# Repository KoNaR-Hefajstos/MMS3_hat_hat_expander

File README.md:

# Hat hat expander

## Sekcja 0: Jak szybko, dobrze i tanio zrobić hata z dokumentacją

Szybka lista punkcików to wyklepania zanim hat magicznie się zrobi

1. **Sprawdź istniejące projekty:** Zobacz czy nie ma już jakiegoś hata który robi co potrzebujesz. Zobacz w forkach i poszukaj na githubie po hashtag'ach, jeśli nie to
2. **Utwórz Fork:** Kliknij przycisk **Fork** w prawym górnym rogu tego repozytorium.

1. **Konfiguracja repozytorium:** Daj mu adekwatną nazwe, i z'clone'uj forka do siebie na pc
2. **Zasady projektowania:**
   * Dokładniejsza dokumentacja znajduje się w Sekcji 2.
   * Do komunikacji możesz używać **wyłącznie** interfejsów: **I2C, SPI oraz UART**.
   * Modyfikuj połączeń złącza chainbus, bus switch'a i EEPROM'a
   * Nie modyfikuj zarysu płytki, otworów montażowych ani pozycji złączy ChainBus.
   * Możesz usunąć złącze XT60, jeśli Twój projekt go nie wymaga.

### Checklista przed zakończeniem projektu
Przed oznaczeniem projektu jako gotowy i wykonaniem ostatecznego commita, upewnij się, że zrealizowałeś poniższe punkty:

- [ ] Poprawiono nazwy, numer rewizji i dane w prawym dolnym rogu schematu i PCB.
- [ ] Dodano podpis autora/autorów oraz aktualny numer wersji na PCB.
- [ ] Zaktualizowano readme (usunąć tą sekcje)
- [ ] Zaktualizowano opis repo żeby opisywał krótko co robi PCB i jakie ma arkusze hierarchiczne do użycia w nowych hat'ach
- [ ] Usunięto z repozytorium zdjęcia z template'a.
- [ ] Wybrano i zaktualizowano licencję projektu **Uwaga: Wstpęnie już są użyte licencje**.
- [ ] Wygenerowano pliki produkcyjne Gerber
- [ ] Zrobiono commit'a i push'a

### Licencja
Co do licencji, wstępnie jest użyta
* Dla template'a - CC0 1.0 Universal  -> Róbcie co chcecie: Zmieniajce, usuńcie mój podpis, zróbcie closed source. Mi jest to obojętne
* PCB - CERN-OHL-W -> Ktoś może to modyfikować i sprzedać, ale musi zostawić projekt open source i ciebie jako twórce
* Software - MIT License -> Ktoś może to modyfikować i sprzedać, musi odnotować ciebie jako twórce ale **NIE MUSI ZOSTAWIĆ OPEN SOURCE**

Jeśli je modyfikujesz, pamiętaj usunać treści starych licencji

---

## Sekcja 1: Dokumentacja Hat'a

### Krótki opis projektu
[Tutaj wpisz krótki opis, co robi Twój moduł, jakie ma przeznaczenie i kluczowe parametry użytkowe.]

### Zgodność ze standardem ChainBus

* ✅ / ❌ Używa złącza ChainBus, nie zmienia jego miejsca ani pinoutu.
* ✅ / ❌ Używa wyłącznie interfejsów I2C, SPI lub UART i nie inicjuje samodzielnie nowych transmisji (Nie jest master'em I2C albo SPI).
* ✅ / ❌ Spełnia wymagania mechaniczne standardu (wymiary PCB, rozstaw otworów).
* ✅ / ❌ Pobiera maksymalny prąd zgodny z ilością na jednego hat'a
* ✅ / ❌ Obsługuje napięcie wejściowe BRD_VIN do wartości 48V.
<!-- Usuń odpowiednie emoji. Wszystkie powinny być na zielono. Jeśli z czymś nie jest zgodny to napisz w jaki sposób -->

### Komunikacja i adresowanie

#### Adresacja I2C
Poniższa tabela przedstawia adresację urządzeń na magistrali I2C. Wszystkie adresy podane są w formacie 7-bitowym.

| Układ (IC)    | Funkcja                               |  Address   |
| :------------ | :------------------------------------ | :--------: |
| **JP3721**    | Sterownik piekarnika                  | `1010000b` |
| **PCAL9535A** | Ekspander GPIO (Dioda LED, Krańcówki) | `0100000b` |
| **TMP102**    | Czujnik temperatury                   | `1001000b` |

#### Magistrala SPI
Urządzenia SPI podłączone są bezpośrednio do magistrali systemowej bez użycia dodatkowych multiplekserów.

| Układ (IC)  | Funkcja                     | chainbus/multiplexer |
| :---------- | :-------------------------- | :------------------: |
| **TMC5160** | Sterownik silnika krokowego |      `chainbus`      |

#### Magistrala UART
Komunikacja szeregowa UART realizowana jest w sposób bezpośredni z układem docelowym.

| Układ (IC)   | Funkcja       | chainbus/multiplexer |
| :----------- | :------------ | :------------------: |
| **ESP32-C3** | Adapter WI-FI |      `chainbus`      |

### Pinout złączy

| Jn     | Co                                         | Jaki pin co robi                                                     |
| :----- | :----------------------------------------- | :------------------------------------------------------------------- |
| **J1** | Zasilanie zewnętrzne silników              | Pin 1: VIN (zasilanie dodatnie)<br>Pin 2: GND (masa zasilania)       |
| **J2** | Wyjście faz silnika krokowego              | Pin 1: Faza A1<br>Pin 2: Faza A2<br>Pin 3: Faza B1<br>Pin 4: Faza B2 |
| **J3** | Wejście czujnika krańcowego (Limit Switch) | Pin 1: Sygnał wejściowy (z rezystorem Pull-Up)<br>Pin 2: GND (masa)  |

### Konfiguracja układu (Zworki/Rezystory)

| Co             | Jak podłączone | Efekt       |
| :------------- | :------------- | :---------- |
| **J1**         | 1-2 zwarte     | Silnik DC   |
|                | rozwarte       | Silnik BLDC |
| **J2**         | 1-2 zwarte     | 3.3V out    |
|                | 2-3 zwarte     | 5V out      |
| **R1, R2, R3** | Wlutowany R1   | 3.3V out    |
|                | Wlutowany R2   | 5V out      |
|                | Wlutowany R3   | VIN out     |

### Szczegółowy opis techniczny
[Tutaj umieść opis działania układu, parametry maksymalne etc]

### Gotowe arkusze hierarchiczne
W projekcie zaprojektowano/użyto następujących arkuszy hierarchicznych:
* [Nazwa arkusza 1] – [Krótki opis funkcjonalności, np. Zasilacz impulsowy 5V] - [ oryginalny/ wzięty z hata XXX]
* [Nazwa arkusza 2] – [Krótki opis] - [ -||- ]

---

## Sekcja 2: Specyfikacja standardu ChainBus

### Architektura i łączenie modułów
Standard ChainBus umożliwia modułowe łączenie hatów. Na jednym MMS3 można zamontować pionowo **do 8 hat'ów**. Połączenie realizowane jest poprzez wpięcie złącza męskiego kolejnego hat'a w złącze żeńskie poprzedniego

### Komunikacja i sterowanie
Magistrala ChainBus jest w pełni cyfrowa. Płyta główna nie steruje bezpośrednio sygnałami ogólnego przeznaczenia (GPIO) na poszczególnych hat'ach. Wszelkie operacje (np. obsługa diod LED, odczyt krańcówek, generowanie sygnałów PWM) muszą być realizowane przez dedykowane układy scalone (np. ekspandery portów, sterowniki) komunikujące się przez interfejsy systemowe.

*Przykład:*
`MCU` $\rightarrow$ `Expander GPIO po I2C` $\rightarrow$ `Dioda LED`

Wybór aktywnego modułu realizowany jest przez układ przełącznika magistrali (bus switch) na płycie głównej. Dzięki temu linie I2C, SPI i UART są niezależne dla każdego hat'a (brak konfliktów adresów I2C między różnymi hatami).
* **Identyfikacja:** Każdy moduł powinien posiadać pamięć EEPROM na magistrali I2C w celu identyfikacji płyty przez system - układ M24C64-W skonfigurowany na adres `1010000` przy liniach adresowych A0, A1, A2 zwartych do masy.

### Zasilanie
Złącze ChainBus dostarcza następujące linie zasilania:

| Magistrala zasilania | Napięcie znamionowe | Maksymalny prąd (łączny dla 8 hatów) | Szacowany prąd na jeden hat |
| :------------------- | :-----------------: | :----------------------------------: | :-------------------------: |
| **5V**               |        5.0 V        |                1.0 A                 |           125 mA            |
| **12V stby**         |       12.0 V        |                0.5 A                 |            65 mA            |
| **BRD_VIN**          |   12.0 V – 48.0 V   |                1.5 A                 |           185 mA            |

*   Komponenty podłączone do linii `BRD_VIN` muszą być przystosowane do pracy z napięciem od 12V do **48 V**.
*   W przypadku zapotrzebowania na wyższą moc, dopuszczalne jest zastosowanie dodatkowego złącza zasilania XT60 (obciążalność do ok. 60 A).

### Wymagania mechaniczne i złącza
* **Wymiary PCB:** Niedozwolona jest zmiana obrysu płytki oraz położenia otworów montażowych, aby zachować kompatybilność mechaniczną.
* **Pozycjonowanie złączy ChainBus:** Położenie złącza standardu 2x16 SMD (raster 2.54 mm) musi być zgodne z szablonem. Złącze żeńskie montowane jest na stronie FRONT, natomiast złącze męskie na stronie BACK.
* **Interfejsy zewnętrzne:** Złącza wejścia/wyjścia (domyślnie standard JST-XH 2.5 mm o obciążalności do 3 A) oraz opcjonalne złącze XT60 powinny być umieszczone przy dolnej krawędzi płytki. Elementy regulacyjne i sygnalizacyjne (potencjometry, przełączniki, diody LED) należy lokalizować przy prawej krawędzi płytki.
* **Komponenty** Wszystkie komponenty powinny być na stronie front płytki żeby nie haczyły o elementy ze wcześniejszego hat'a

---

## Sekcja 3: Licencja, linki i tagi

### Licencjonowanie projektu

*   **PCB:** [CERN-OHL-W](https://ohwr.org/project/cernohl/wikis/Documents/CERN-OHL-version-2) - Umożliwia modyfikacje i sprzedaż, ale musi pozostawić oryginalnego autora i zmiany muszą być open source
*   **Software:** [MIT License](https://opensource.org/licenses/MIT) - Umożliwia modyfikacje i sprzedaż, ale musi pozostawić oryginalnego autora. Zmiany **nie muszą być open source**

[Template](https://github.com/KoNaR-Hefajstos/MMS3_hat_templates/) jest na licencji CC0 1.0 Universal. **Reszta projektu nie jest na tej licencji**
### Tagi projektu
#chainbus #MMS3 #ModuCard

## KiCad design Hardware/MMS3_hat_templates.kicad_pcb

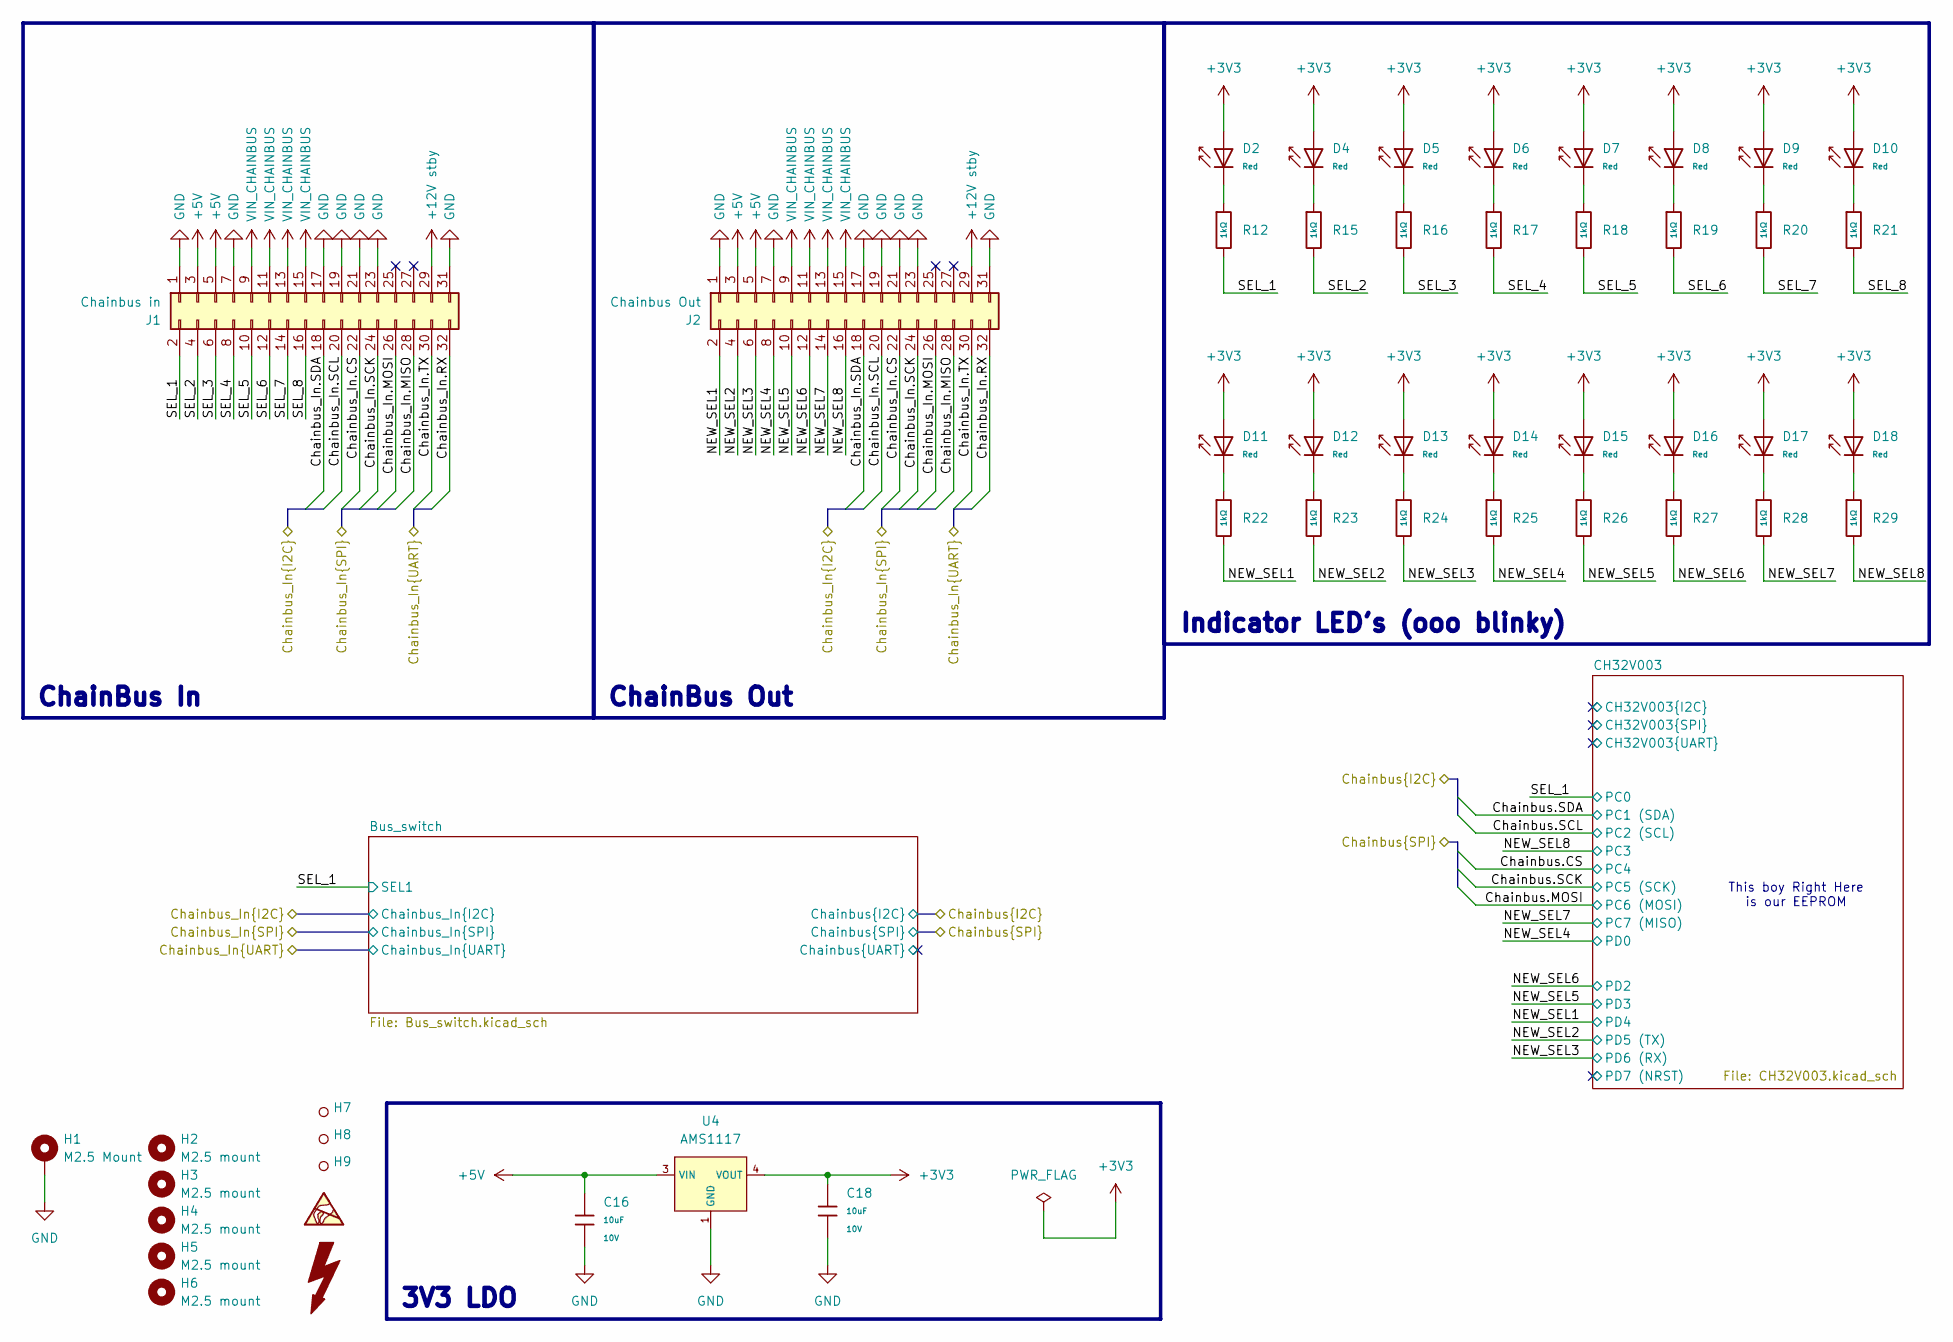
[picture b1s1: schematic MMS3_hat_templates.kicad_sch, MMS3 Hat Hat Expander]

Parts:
C16, C18: 10uF; C_0603; Voltage Rated 10V; Tolerance ±10%; Part CL10A106KP8NNNC; LCSC C19702
D2, D4, D5, D6, D7, D8, D9, D10, D11, D12, D13, D14, D15, D16, D17, D18: Red; D_0603; Part KT-0603R; LCSC C2286
H1: M2.5 Mount; MountingHole_2.7mm_M2.5_DIN965_Pad_TopOnly
H2, H3, H4, H5, H6: M2.5 mount; MountingHole_2.7mm_M2.5
H7, H8, H9: Hole_Tooling_JLCPCB
J1: Chainbus in; PinHeader_2x16_P2.54mm_Vertical_SMD
J2: Chainbus Out; PinSocket_2x16_P2.54mm_Vertical_SMD
R12, R15, R16, R17, R18, R19, R20, R21, R22, R23, R24, R25, R26, R27, R28, R29: 1kΩ; R_0603; Overload Voltage (Max) 75V; Tolerance ±1%; Part 0603WAF1001T5E; LCSC C21190
U4: AMS1117; SOT-223-3_L6.5-W3.4-P2.30-LS7.0-BR; Output Voltage 3.3V; Dropout Voltage 1.3V@(800mA); Part AMS1117-3.3; LCSC C6186

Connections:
+3V3: C18.1, D2.2, D4.2, D5.2, D6.2, D7.2, D8.2, D9.2, D10.2, D11.2, D12.2, D13.2, D14.2, D15.2, D16.2, D17.2, D18.2, U4.2 (VOUT), U4.4 (VOUT); also elsewhere on the board
+5V: C16.1, J1.3, J1.5, J2.3, J2.5, U4.3 (VIN)
+12V stby: J1.29, J2.29
/Chainbus_In.CS: J1.22, J2.22; also elsewhere on the board
/Chainbus_In.MISO: J1.28, J2.28; also elsewhere on the board
/Chainbus_In.MOSI: J1.26, J2.26; also elsewhere on the board
/Chainbus_In.RX: J1.32, J2.32; also elsewhere on the board
/Chainbus_In.SCK: J1.24, J2.24; also elsewhere on the board
/Chainbus_In.SCL: J1.20, J2.20; also elsewhere on the board
/Chainbus_In.SDA: J1.18, J2.18; also elsewhere on the board
/Chainbus_In.TX: J1.30, J2.30; also elsewhere on the board
/NEW_SEL1: J2.2, R22.2; also elsewhere on the board
/NEW_SEL2: J2.4, R23.2; also elsewhere on the board
/NEW_SEL3: J2.6, R24.2; also elsewhere on the board
/NEW_SEL4: J2.8, R25.2; also elsewhere on the board
/NEW_SEL5: J2.10, R26.2; also elsewhere on the board
/NEW_SEL6: J2.12, R27.2; also elsewhere on the board
/NEW_SEL7: J2.14, R28.2; also elsewhere on the board
/NEW_SEL8: J2.16, R29.2; also elsewhere on the board
/SEL_1: J1.2, R12.2; also elsewhere on the board
/SEL_2: J1.4, R15.2
/SEL_3: J1.6, R16.2
/SEL_4: J1.8, R17.2
/SEL_5: J1.10, R18.2
/SEL_6: J1.12, R19.2
/SEL_7: J1.14, R20.2
/SEL_8: J1.16, R21.2
GND: C16.2, C18.2, H1.1 (1_1), J1.1, J1.7, J1.17, J1.19, J1.21, J1.23, J1.31, J2.1, J2.7, J2.17, J2.19, J2.21, J2.23, J2.31, U4.1 (GND); also elsewhere on the board
unnamed: D2.1, R12.1
unnamed: D4.1, R15.1
unnamed: D5.1, R16.1
unnamed: D6.1, R17.1
unnamed: D7.1, R18.1
unnamed: D8.1, R19.1
unnamed: D9.1, R20.1
unnamed: D10.1, R21.1
unnamed: D11.1, R22.1
unnamed: D12.1, R23.1
unnamed: D13.1, R24.1
unnamed: D14.1, R25.1
unnamed: D15.1, R26.1
unnamed: D16.1, R27.1
unnamed: D17.1, R28.1
unnamed: D18.1, R29.1
VIN_CHAINBUS: J1.9, J1.11, J1.13, J1.15, J2.9, J2.11, J2.13, J2.15

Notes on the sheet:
This boy Right Here is our EEPROM
ChainBus In
Indicator LED's (ooo blinky)
ChainBus Out
3V3 LDO

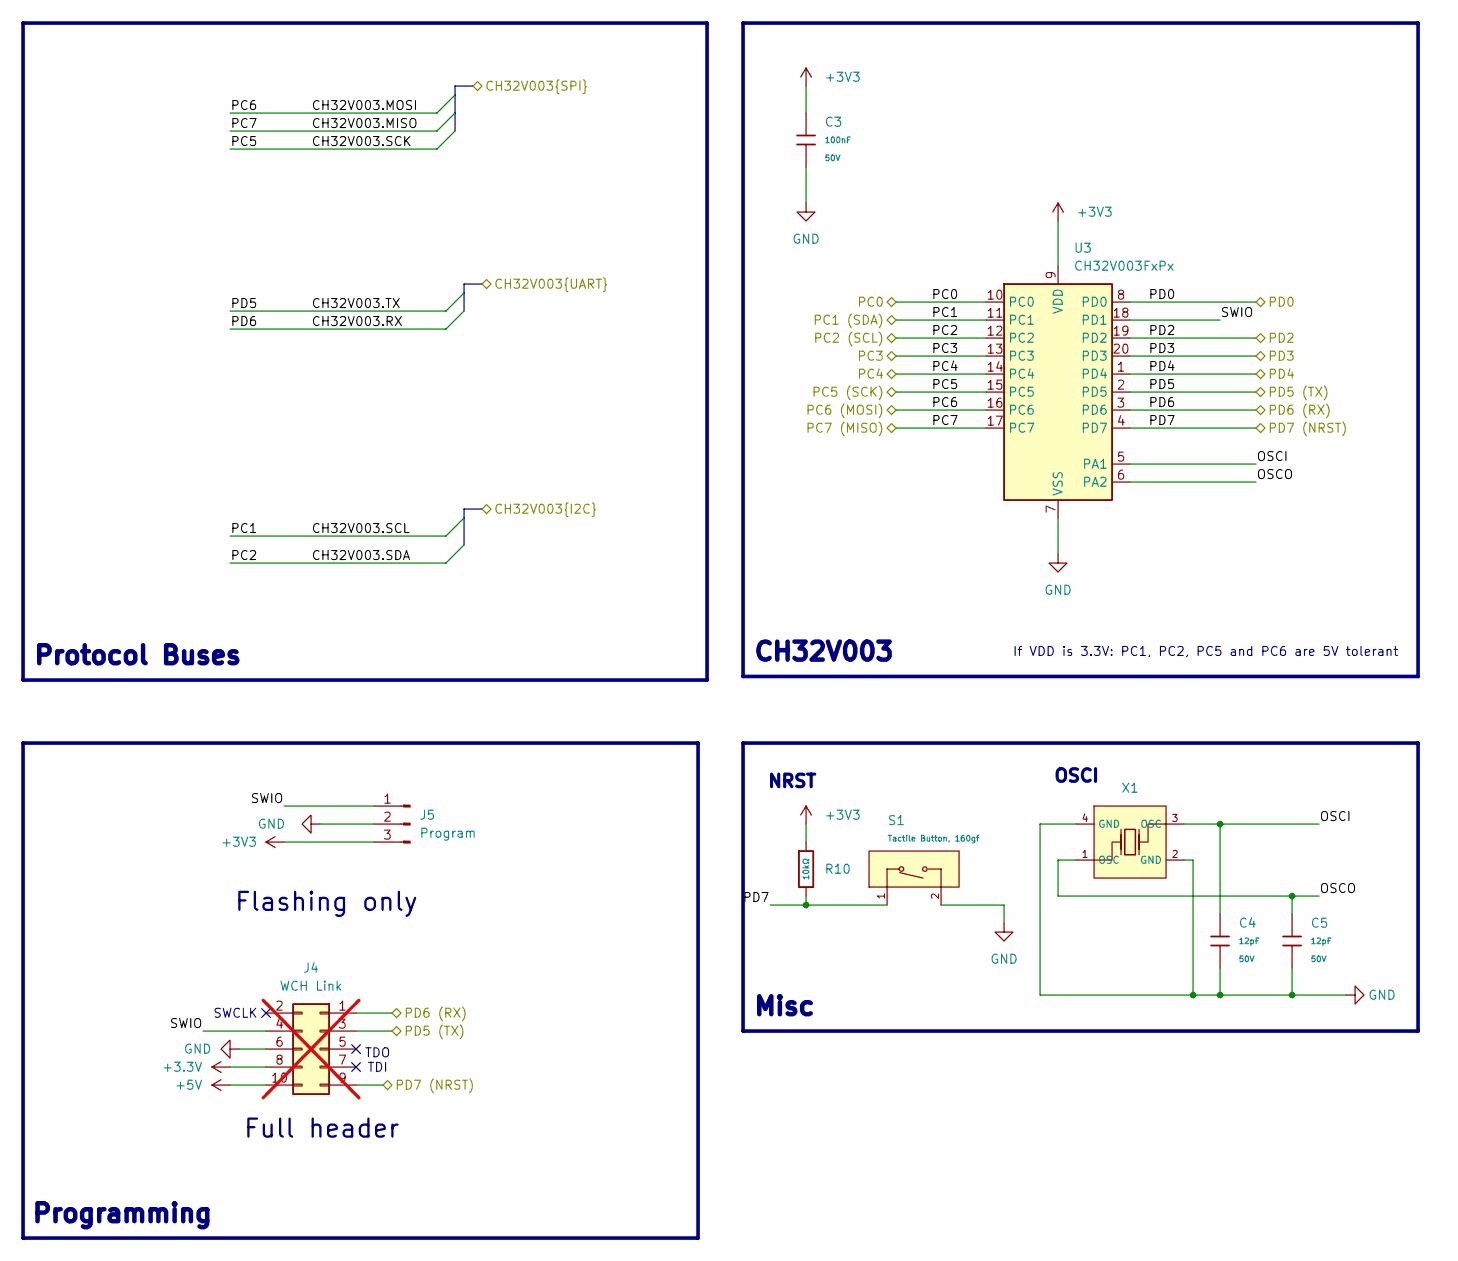
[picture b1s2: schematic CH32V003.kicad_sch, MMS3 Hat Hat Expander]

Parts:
C3: 100nF; C_0603; Voltage Rated 50V; Tolerance ±10%; Part CC0603KRX7R9BB104; LCSC C14663
C4, C5: 12pF; C_0603; Voltage Rated 50V; Tolerance ±5%; Part CL10C120JB8NNNC; LCSC C38523
J4: WCH Link; PinSocket_2x05_P2.54mm_Vertical; not fitted
J5: Program; PinHeader_1x03_P2.54mm_Vertical
R10: 10kΩ; R_0603; Overload Voltage (Max) 75V; Tolerance ±1%; Part 0603WAF1002T5E; LCSC C25804
S1: Tactile Button, 160gf; SW_TS-1088-AR02016; Voltage Rating (Dc) 12V; Part TS-1088-AR02016; LCSC C720477
U3: CH32V003FxPx; TSSOP-20_4.4x6.5mm_P0.65mm
X1: X322525MOB4SI; OSC-SMD_4P-L3.2-W2.5-BL; Frequency Tolerance ±10ppm; Part X322525MOB4SI; LCSC C9006

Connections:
+3V3: C3.1, J5.3, R10.1, U3.9 (VDD); also elsewhere on the board
/CH32V003/OSCI: C4.1, U3.5 (PA1), X1.3 (OSC)
/CH32V003/OSCO: C5.1, U3.6 (PA2), X1.1 (OSC)
/CH32V003/PD7: J4.9, R10.2, S1.1 (A), U3.4 (PD7)
/CH32V003/SWIO: J4.4, J5.1, U3.18 (PD1)
/Chainbus.CS: U3.14 (PC4); also elsewhere on the board
/Chainbus.MOSI: U3.16 (PC6); also elsewhere on the board
/Chainbus.SCK: U3.15 (PC5); also elsewhere on the board
/Chainbus.SCL: U3.12 (PC2); also elsewhere on the board
/Chainbus.SDA: U3.11 (PC1); also elsewhere on the board
/NEW_SEL1: U3.1 (PD4); also elsewhere on the board
/NEW_SEL2: J4.3, U3.2 (PD5); also elsewhere on the board
/NEW_SEL3: J4.1, U3.3 (PD6); also elsewhere on the board
/NEW_SEL4: U3.8 (PD0); also elsewhere on the board
/NEW_SEL5: U3.20 (PD3); also elsewhere on the board
/NEW_SEL6: U3.19 (PD2); also elsewhere on the board
/NEW_SEL7: U3.17 (PC7); also elsewhere on the board
/NEW_SEL8: U3.13 (PC3); also elsewhere on the board
/SEL_1: U3.10 (PC0); also elsewhere on the board
GND: C3.2, C4.2, C5.2, J4.6, J5.2, S1.2 (B), U3.7 (VSS), X1.2 (GND), X1.4 (GND); also elsewhere on the board

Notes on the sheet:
NRST
Full header
SWCLK
If VDD is 3.3V: PC1, PC2, PC5 and PC6 are 5V tolerant
CH32V003
Flashing only
OSCI
Protocol Buses
Misc
Programming
TDO TDI

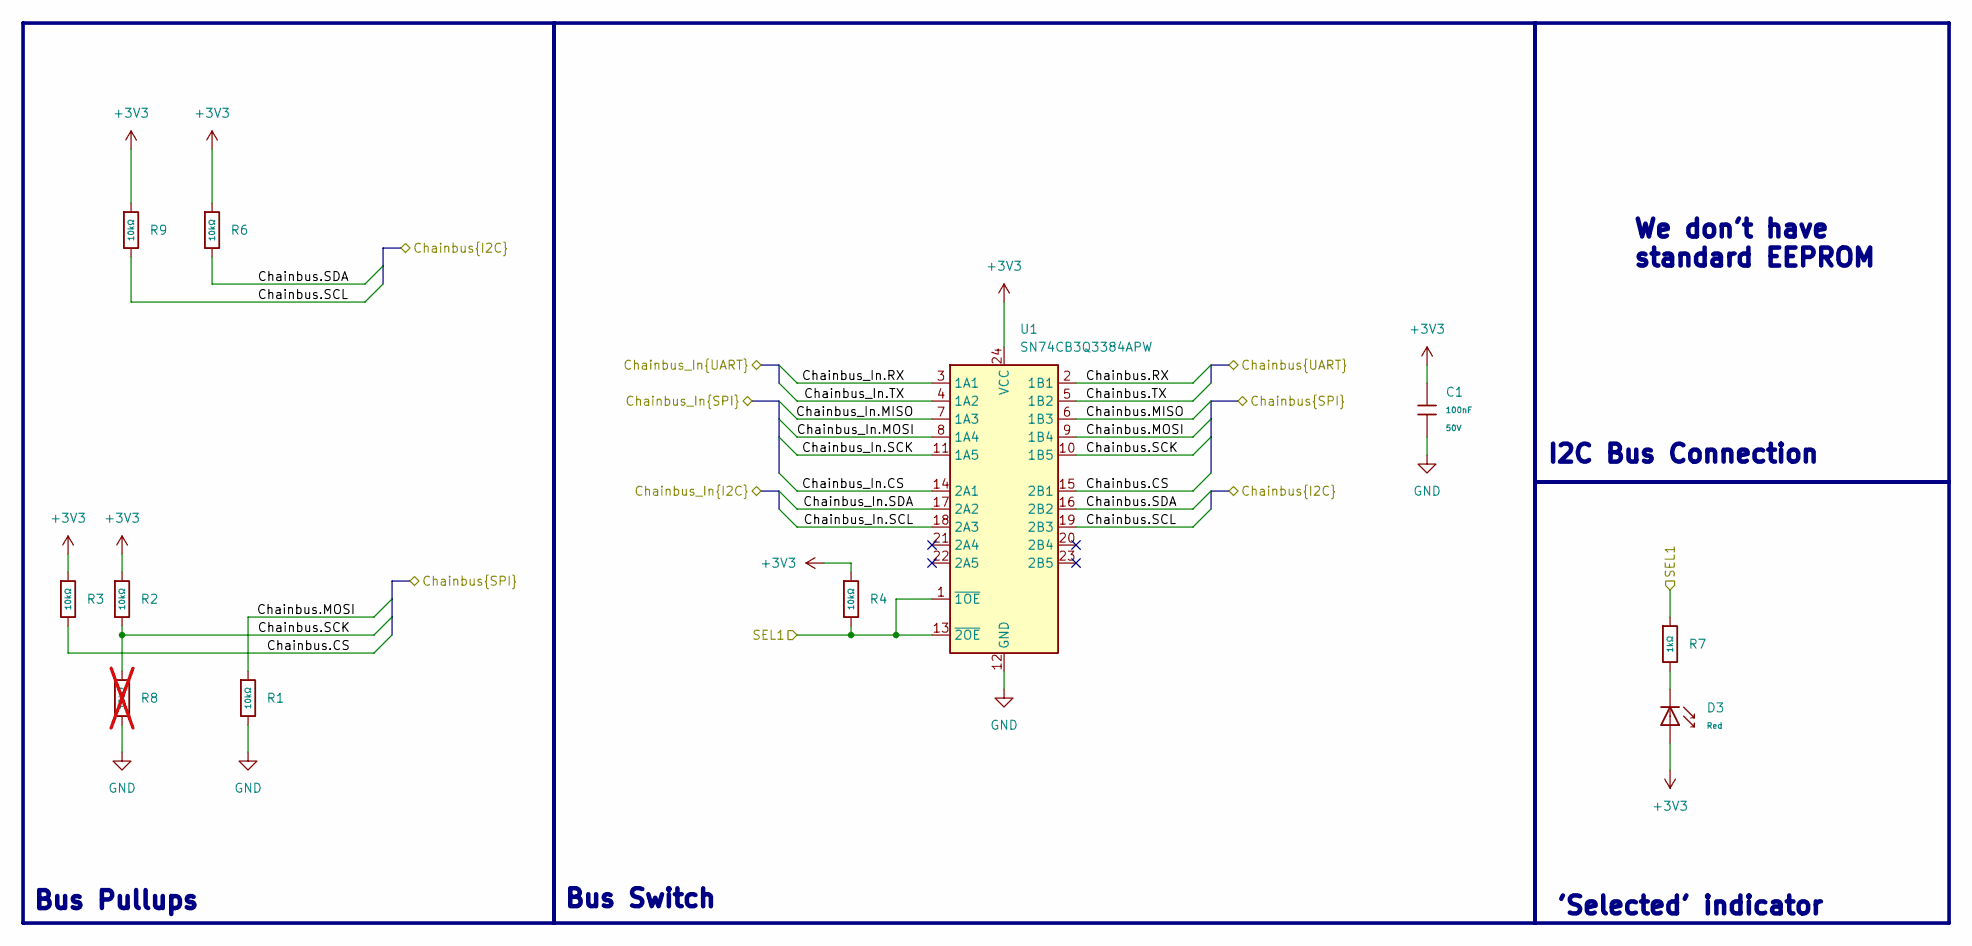
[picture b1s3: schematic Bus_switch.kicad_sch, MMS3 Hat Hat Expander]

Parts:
C1: 100nF; C_0603; Voltage Rated 50V; Tolerance ±10%; Part CC0603KRX7R9BB104; LCSC C14663
D3: Red; D_0603; Part KT-0603R; LCSC C2286
R1, R2, R3, R4, R6, R9: 10kΩ; R_0603; Overload Voltage (Max) 75V; Tolerance ±1%; Part 0603WAF1002T5E; LCSC C25804
R7: 1kΩ; R_0603; Overload Voltage (Max) 75V; Tolerance ±1%; Part 0603WAF1001T5E; LCSC C21190
R8: 10kΩ; R_0603; Overload Voltage (Max) 75V; Tolerance ±1%; Part 0603WAF1002T5E; LCSC C25804; not fitted
U1: SN74CB3Q3384APW; TSSOP-24_4.4x7.8mm_P0.65mm; LCSC C469874

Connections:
+3V3: C1.1, D3.2, R2.1, R3.1, R4.1, R6.1, R9.1, U1.24 (VCC); also elsewhere on the board
/Bus_switch/Chainbus.RX: U1.2 (1B1)
/Bus_switch/Chainbus.TX: U1.5 (1B2)
/Chainbus.CS: R3.2, U1.15 (2B1); also elsewhere on the board
/Chainbus.MISO: U1.6 (1B3)
/Chainbus.MOSI: R1.1, U1.9 (1B4); also elsewhere on the board
/Chainbus.SCK: R2.2, R8.1, U1.10 (1B5); also elsewhere on the board
/Chainbus.SCL: R9.2, U1.19 (2B3); also elsewhere on the board
/Chainbus.SDA: R6.2, U1.16 (2B2); also elsewhere on the board
/Chainbus_In.CS: U1.14 (2A1); also elsewhere on the board
/Chainbus_In.MISO: U1.7 (1A3); also elsewhere on the board
/Chainbus_In.MOSI: U1.8 (1A4); also elsewhere on the board
/Chainbus_In.RX: U1.3 (1A1); also elsewhere on the board
/Chainbus_In.SCK: U1.11 (1A5); also elsewhere on the board
/Chainbus_In.SCL: U1.18 (2A3); also elsewhere on the board
/Chainbus_In.SDA: U1.17 (2A2); also elsewhere on the board
/Chainbus_In.TX: U1.4 (1A2); also elsewhere on the board
/SEL_1: R4.2, R7.1, U1.1 (~1OE), U1.13 (~2OE); also elsewhere on the board
GND: C1.2, R1.2, R8.2, U1.12 (GND); also elsewhere on the board
unnamed: D3.1, R7.2

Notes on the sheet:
Bus Switch
'Selected' indicator
Bus Pullups
We don't have standard EEPROM
I2C Bus Connection

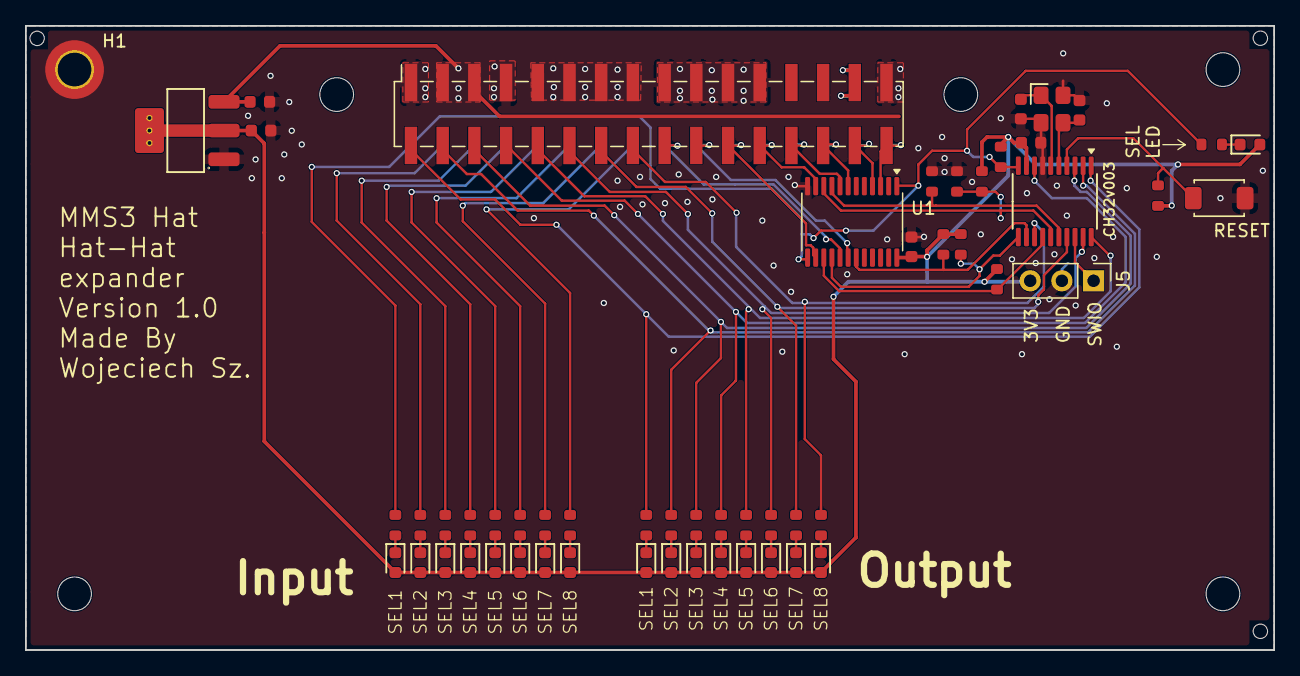
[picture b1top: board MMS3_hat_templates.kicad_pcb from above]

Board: 2 copper layers, 100.0 x 50.0 mm, 65 parts (1 on the bottom side), 55 nets.

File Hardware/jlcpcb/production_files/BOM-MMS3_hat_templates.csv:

Comment,Designator,Footprint,LCSC,Quantity
100nF,"C1,C3",C_0603,C14663,2
10kΩ,"R1,R10,R2,R3,R4,R6,R9",R_0603,C25804,7
10uF,"C16,C18",C_0603,C19702,2
12pF,"C4,C5",C_0603,C38523,2
1kΩ,"R12,R15,R16,R17,R18,R19,R20,R21,R22,R23,R24,R25,R26,R27,R28,R29,R7",R_0603,C21190,17
AMS1117,U4,SOT-223-3_L6.5-W3.4-P2.30-LS7.0-BR,C6186,1
Red,"D10,D11,D12,D13,D14,D15,D16,D17,D18,D2,D3,D4,D5,D6,D7,D8,D9",D_0603,C2286,17
SN74CB3Q3384APW,U1,TSSOP-24_4.4x7.8mm_P0.65mm,C469874,1
"Tactile Button, 160gf",S1,SW_TS-1088-AR02016,C720477,1
X322525MOB4SI,X1,OSC-SMD_4P-L3.2-W2.5-BL,C9006,1
CH32V003FxPx,U3,TSSOP-20_4.4x6.5mm_P0.65mm,,1
Chainbus Out,J2,PinSocket_2x16_P2.54mm_Vertical_SMD,,1
~,H8,Hole_Tooling_JLCPCB,,1
~,H7,Hole_Tooling_JLCPCB,,1
~,H9,Hole_Tooling_JLCPCB,,1
Program,J5,PinHeader_1x03_P2.54mm_Vertical,,1
Chainbus in,J1,PinHeader_2x16_P2.54mm_Vertical_SMD,,1
